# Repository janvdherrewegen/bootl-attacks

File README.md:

# Fill your Boots: Enhanced Embedded Bootloader Exploits via Fault Injection and Binary Analysis

This repository contains source code and data to reproduce results from our paper "Fill your Boots: Enhanced Embedded Bootloader Exploits via Fault Injection and Binary Analysis" at [CHES2021](https://ches.iacr.org/2021/)

## Abstract
The bootloader of an embedded microcontroller is responsible for guarding the device’s internal (flash) memory, enforcing read/write protection mechanisms. Fault injection techniques such as voltage or clock glitching have been proven successful in bypassing such protection for specific microcontrollers, but this often requires expensive equipment and/or exhaustive search of the fault parameters. When multiple glitches are required (e.g., when countermeasures are in place) this search becomes of exponential complexity and thus infeasible. Another challenge which makes embedded bootloaders notoriously hard to analyse is their lack of debugging capabilities.This paper proposes a grey-box approach that leverages binary analysis and advanced software exploitation techniques combined with voltage glitching to develop a powerful attack methodology against embedded bootloaders. We showcase our techniques with three real-world microcontrollers as case studies: 1) we combine static and on-chip dynamic analysis to enable a Return-Oriented Programming exploit on the bootloader of the NXP LPC microcontrollers; 2) we leverage on-chip dynamic analysis on the bootloader of the popular STM8 microcontrollers to constrain the glitch parameter search, achieving the first fully-documented multi-glitch attack on a real-world target; 3) we apply symbolic execution to precisely aim voltage glitches at target instructions based on the execution path in the bootloader of the Renesas 78K0 automotive microcontroller. For each case study, we show that using inexpensive, open-design equipment, we are able to efficiently breach the security of these microcontrollers and get full control of the protected memory, even when multiple glitches are required. Finally, we identify and elaborate on several vulnerable design patterns that should be avoided when implementing embedded bootloaders.

## Dependencies
We use several open source tools and packages to compile and run code on the targets. 

- [k0dasm](https://github.com/mnaberez/k0dasm): A disassembler for the 78k0 
- [as78k0](http://shop-pdp.net/ashtml/as78k0.htm): A compiler for the 78k0
- [aslink](http://shop-pdp.net/ashtml/aslink.htm): A linker for the 78k0
- [sdcc](http://sdcc.sourceforge.net/): Compiler for the stm8
- [naken\_asm](https://github.com/mikeakohn/naken_asm): A disassembler for the stm8
- [stm8flash](https://github.com/vdudouyt/stm8flash):  To flash the stm8 firmware

## Running the code
For the voltage glitching, we use a Raspberry pi3B+ to interface with the GIAnT and the chip under test (cf [Glitch setup](glitch_setup.pdf)). The schematics and source for the GIAnT board is located in the [giant-hardware](giant-hardware) folder.

## Directory Organisation
```
├── 78k0: Code for the 78k0 bootloader analysis (including the symbolic execution framework and glitching code)
├── giant-hardware: Hardware schematics for the new GIAnT board
├── giant-python: Python interface for the GIAnT board
├── lpc: Directory containing the LPC exploit
├── stm8: Code for glitching the STM8
├── README.md
```

## Paper artifacts
The table below clarifies how to recreate the results mentioned in the paper.

| Section | Directory | Commands | Comment |
| ------- | --------- | -------- | ------- |
| 3.2 | ```lpc/ROP``` | ```python3 rop.py```| CRP1 bypass with stack overwrite |
| 3.3 | ```lpc/partial_overwrite``` | ```python3 partial_overwrite.py```| CRP1 bypass with partial flash overwrite |
| 4.1 | ```stm8``` | ```make -C bootloader/```<br>```./flash.sh bootloader/bl_dump.hex option_bytes/STM8AF/opt-rop0-bl0.bin stm8a```| This will flash a firmware to the stm8 which dumps the memory space containing the bootloader over UART |
| 4.2 | ```stm8``` | ```make -C profiling/```<br>```./flash.sh profiling/enter_app.hex option_bytes/STM8AF/opt-rop0-bl0.bin stm8a```<br>```python stm8af_glitch profile``` | This flashes the profiling code and introduces glitches triggered on a GPIO pin |
| 4.3 | ```stm8``` | ```python stm8l_glitch partial_attack``` | Run the glitching on the partially protected stm8l MCU. |
| 4.4 | ```stm8``` | ```python stm8af_glitch full_attack```<br>```python stm8l_glitch full_attack```| Runs the double glitch attack on the STM8 MCUs  |
| 5.1 | ```78k0``` | ```make -C bootloader_dump/```<br>```python glitching/renesas_fpi.py program bootloader/dump_bootl.bin``` | Compiles the code for dumping the 78k0 bootloader. Once flashed, it transmits the code over UART |
| 5.3 | ```78k0/path_constraint``` | ```python2 main.py --db testcases/78k0/checksum_handler.p``` | This command generates the equivalence classes for the checksum handler based on the path through the firmware |
| 5.3 | ```78k0/glitching``` | ```python renesas-78k0-glitch.py``` | This script glitches the checksum command for all equivalence classes output by the path_constraint module |

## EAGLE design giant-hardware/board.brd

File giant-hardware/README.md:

# GIAnT Hardware

This directory contains the schematics for the revised GIAnT board. In line with the previous version, it still uses the (now deprecated) [ZTEX USB-FPGA Module 1.11](https://www.ztex.de/usb-fpga-1/usb-fpga-1.11.e.html). New adopters can order the following components for an alternative:

- [USB-FPGA Module 2.04](https://www.ztex.de/usb-fpga-2/usb-fpga-2.04.e.html): 99 EUR
- [Series 1 Adapter](https://www.ztex.de/usb-fpga-2/1-adapter.e.html): 8 EUR

Including the PCB and all other components, the hardware can be assembled for ~200 USD. [BOM.txt](BOM.txt) contains a detailed Bill of Materials.

## Specifications
With the original composition, the GIAnT offers the following capabilities:

- 10ns minimum pulse width
- 10ns minimum pulse offset
- 145mA max current draw (limited by the [THS3062](https://www.ti.com/store/ti/en/p/product/?p=THS3062D) opamp)

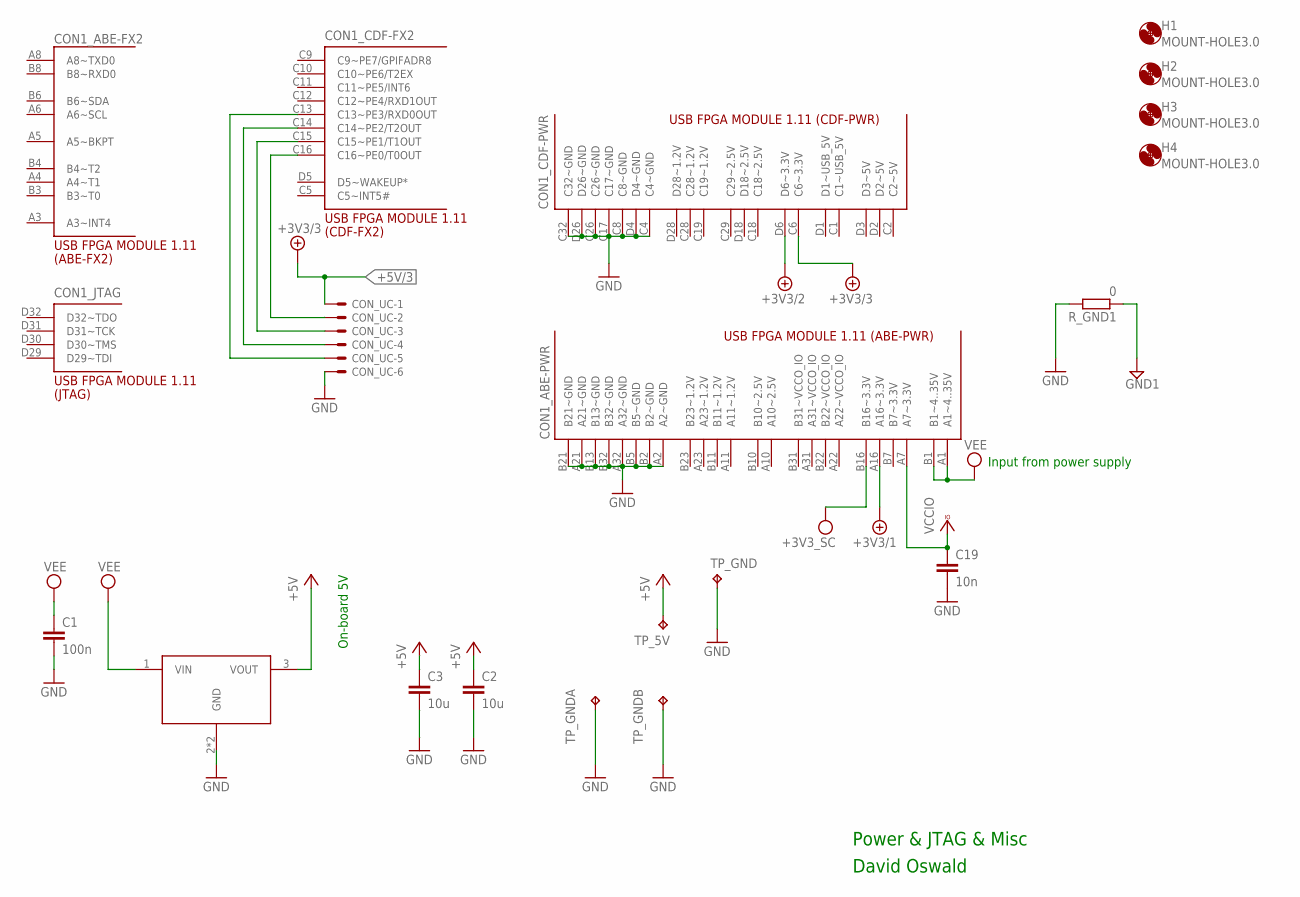
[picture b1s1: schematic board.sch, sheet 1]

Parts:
C1: 100n; C0805K
C2, C3: 10u; C0805K
C19: 10n; C0805K
CON1: USB-FPGA1.11
CON_UC: 22-23-2061
H1, H2, H3, H4: MOUNT-HOLE3.0; 3,0
R_GND1: 0; R0805
TP_5V: TPB1,27; B1,27
TP_GND: TPB1,27; B1,27
TP_GNDA: TPPAD1-13; P1-13
TP_GNDB: TPPAD1-13; P1-13
U$1: MIC5209; SOT223-3

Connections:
+5V: C2.1, C3.1, TP_5V.TP, U$1.3 (VOUT); also elsewhere on the board
+5V/1: CON1.A16 (A16~3.3V); also elsewhere on the board
+5V/2: CON1.D6 (D6~3.3V); also elsewhere on the board
+5V/3: CON1.C6 (C6~3.3V), CON_UC.1; also elsewhere on the board
GND: C1.2, C2.2, C3.2, C19.2, CON1.A2 (A2~GND), CON1.A21 (A21~GND), CON1.A32 (A32~GND), CON1.B2 (B2~GND), CON1.B5 (B5~GND), CON1.B13 (B13~GND), CON1.B21 (B21~GND), CON1.B32 (B32~GND), CON1.C4 (C4~GND), CON1.C8 (C8~GND), CON1.C17 (C17~GND), CON1.C26 (C26~GND), CON1.C32 (C32~GND), CON1.D4 (D4~GND), CON1.D26 (D26~GND), CON_UC.6, R_GND1.2, TP_GND.TP, TP_GNDA.TP, TP_GNDB.TP, U$1.2 (GND), U$1.4 (GND); also elsewhere on the board
GND1: R_GND1.1; also elsewhere on the board
unnamed: CON1.C13 (C13~PE3/RXD0OUT), CON_UC.5
unnamed: CON1.C14 (C14~PE2/T2OUT), CON_UC.4
unnamed: CON1.C15 (C15~PE1/T1OUT), CON_UC.3
unnamed: CON1.C16 (C16~PE0/T0OUT), CON_UC.2
VCCIO: C19.1, CON1.A7 (A7~3.3V); also elsewhere on the board
VEE: C1.1, CON1.A1 (A1~4..35V), CON1.B1 (B1~4..35V), U$1.1 (VIN)
VPP: CON1.B16 (B16~3.3V); also elsewhere on the board

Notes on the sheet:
David Oswald
Power & JTAG & Misc
On-board 5V
Input from power supply

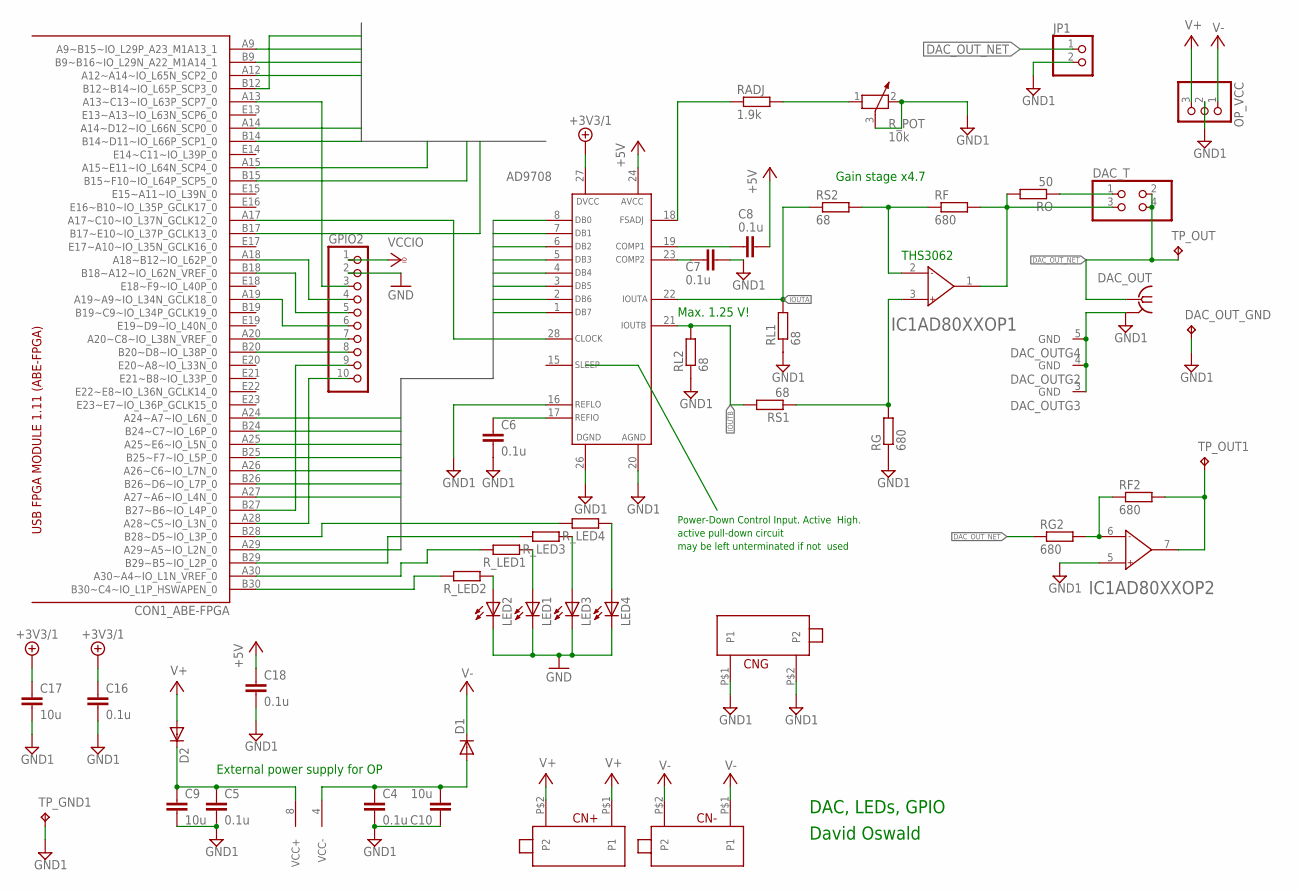
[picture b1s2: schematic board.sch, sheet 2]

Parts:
AD9708: AD7908; SO28W
C4, C5, C6, C7, C8, C16, C18: 0.1u; C0805K
C9, C10, C17: 10u; C0805K
CN+: 24243; 24_243
CN-: 24243; 24_243
CNG: 24243; 24_243
CON1: USB-FPGA1.11
D1, D2: DIODE-SOD123; SOD123
DAC_OUT: BU-SMA-V
DAC_OUT_GND: TPB1,27; B1,27
DAC_T: PINHD-2X2; 2X02
GPIO2: PINHD-1X10; 1X10
IC1: AD80XX; SO08
JP1: PINHD-1X2; 1X02
LED1, LED2, LED3, LED4: LEDCHIPLED_0805; CHIPLED_0805
OP_VCC: PINHD-1X3; 1X03
RADJ: 1.9k; R0805
RF, RF2: 680; R0805
RG, RG2: 680; R0805
RL1, RL2: 68; R0805
RO: 50; R0805
RS1, RS2: 68; R0805
R_LED1, R_LED2, R_LED3, R_LED4: R-EU_R0805; R0805
R_POT: 10k; PT-SPIN
TP_GND1: TPB1,27; B1,27
TP_OUT, TP_OUT1: TPB1,27; B1,27

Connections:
+5V: AD9708.24 (AVCC), C8.1, C18.1; also elsewhere on the board
+5V/1: AD9708.27 (DVCC), C16.1, C17.1; also elsewhere on the board
CLK: AD9708.28 (CLOCK), CON1.A17 (A17~C10~IO_L37N_GCLK12_0)
CLK_SC: CON1.A15 (A15~E11~IO_L64N_SCP4_0); also elsewhere on the board
COMP1: AD9708.19 (COMP1), C8.2
COMP2: AD9708.23 (COMP2), C7.1
DAC_OUT_NET: DAC_OUT.1, DAC_T.2, DAC_T.4, JP1.1, RG2.1, TP_OUT.TP
DB0: AD9708.8 (DB0), CON1.A29 (A29~A5~IO_L2N_0)
DB1: AD9708.7 (DB1), CON1.A27 (A27~A6~IO_L4N_0)
DB2: AD9708.6 (DB2), CON1.B26 (B26~D6~IO_L7P_0)
DB3: AD9708.5 (DB3), CON1.A26 (A26~C6~IO_L7N_0)
DB4: AD9708.4 (DB4), CON1.A25 (A25~E6~IO_L5N_0)
DB5: AD9708.3 (DB5), CON1.B25 (B25~F7~IO_L5P_0)
DB6: AD9708.2 (DB6), CON1.A24 (A24~A7~IO_L6N_0)
DB7: AD9708.1 (DB7), CON1.B24 (B24~C7~IO_L6P_0)
FSADJ: AD9708.18 (FSADJ), RADJ.1
GND: GPIO2.2, LED1.C, LED2.C, LED3.C, LED4.C; also elsewhere on the board
GND1: AD9708.16 (REFLO), AD9708.20 (AGND), AD9708.26 (DGND), C4.2, C5.2, C6.2, C7.2, C9.2, C10.1, C16.2, C17.2, C18.2, CNG.P$1 (P1), CNG.P$2 (P2), DAC_OUT.2 (GND), DAC_OUT.3 (GND), DAC_OUT.4 (GND), DAC_OUT.5 (GND), DAC_OUT_GND.TP, IC1.5 (IN+), JP1.2, OP_VCC.2, RG.1, RL1.1, RL2.1, R_POT.2, R_POT.3, TP_GND1.TP; also elsewhere on the board
IO: CON1.B9 (B9~B16~IO_L29N_A22_M1A14_1); also elsewhere on the board
IOUTA: AD9708.22 (IOUTA), RL1.2, RS2.1
IOUTB: AD9708.21 (IOUTB), RL2.2, RS1.2
unnamed: CON1.A13 (A13~C13~IO_L63P_SCP7_0), GPIO2.3
unnamed: CON1.A18 (A18~B12~IO_L62P_0), GPIO2.4
unnamed: CON1.B18 (B18~A12~IO_L62N_VREF_0), GPIO2.5
unnamed: CON1.A19 (A19~A9~IO_L34N_GCLK18_0), GPIO2.6
unnamed: CON1.A20 (A20~C8~IO_L38N_VREF_0), GPIO2.7
unnamed: CON1.B20 (B20~D8~IO_L38P_0), GPIO2.8
unnamed: CON1.B27 (B27~B6~IO_L4P_0), GPIO2.9
unnamed: CON1.A28 (A28~C5~IO_L3N_0), GPIO2.10
unnamed: IC1.3 (IN+), RG.2, RS1.1
unnamed: IC1.2 (IN-), RF.1, RS2.2
unnamed: DAC_T.3, IC1.1 (OUT), RF.2, RO.2
unnamed: DAC_T.1, RO.1
unnamed: RADJ.2, R_POT.1
unnamed: IC1.6 (IN-), RF2.1, RG2.2
unnamed: IC1.7 (OUT), RF2.2, TP_OUT1.TP
unnamed: LED2.A, R_LED2.1
unnamed: LED1.A, R_LED1.1
unnamed: LED3.A, R_LED3.1
unnamed: LED4.A, R_LED4.1
unnamed: CON1.B30 (B30~C4~IO_L1P_HSWAPEN_0), R_LED2.2
unnamed: CON1.A30 (A30~A4~IO_L1N_VREF_0), R_LED1.2
unnamed: CON1.B29 (B29~B5~IO_L2P_0), R_LED3.2
unnamed: CON1.B28 (B28~D5~IO_L3P_0), R_LED4.2
PIN4: CON1.B14 (B14~D11~IO_L66P_SCP1_0); also elsewhere on the board
PIN6: CON1.A12 (A12~A14~IO_L65N_SCP2_0); also elsewhere on the board
PIN8: CON1.A9 (A9~B15~IO_L29P_A23_M1A13_1); also elsewhere on the board
REFIO: AD9708.17 (REFIO), C6.1
RST: CON1.B15 (B15~F10~IO_L64P_SCP5_0); also elsewhere on the board
SHDN: CON1.B17 (B17~E10~IO_L37P_GCLK13_0); also elsewhere on the board
SW1: CON1.B12 (B12~B14~IO_L65P_SCP3_0)
SW2: CON1.A14 (A14~D12~IO_L66N_SCP0_0)
V+: CN+.P$1 (P1), CN+.P$2 (P2), D2.A, OP_VCC.3
V-: CN-.P$1 (P1), CN-.P$2 (P2), D1.C, OP_VCC.1
VCC+: C5.1, C9.1, D2.C, IC1.8 (VCC+)
VCC-: C4.1, C10.2, D1.A, IC1.4 (VCC-)
VCCIO: GPIO2.1; also elsewhere on the board

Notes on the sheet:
David Oswald
DAC, LEDs, GPIO
Max. 1.25 V!
Gain stage x4.7
Power-Down Control Input. Active High.
active pull-down circuit
may be left unterminated if not used
THS3062
External power supply for OP

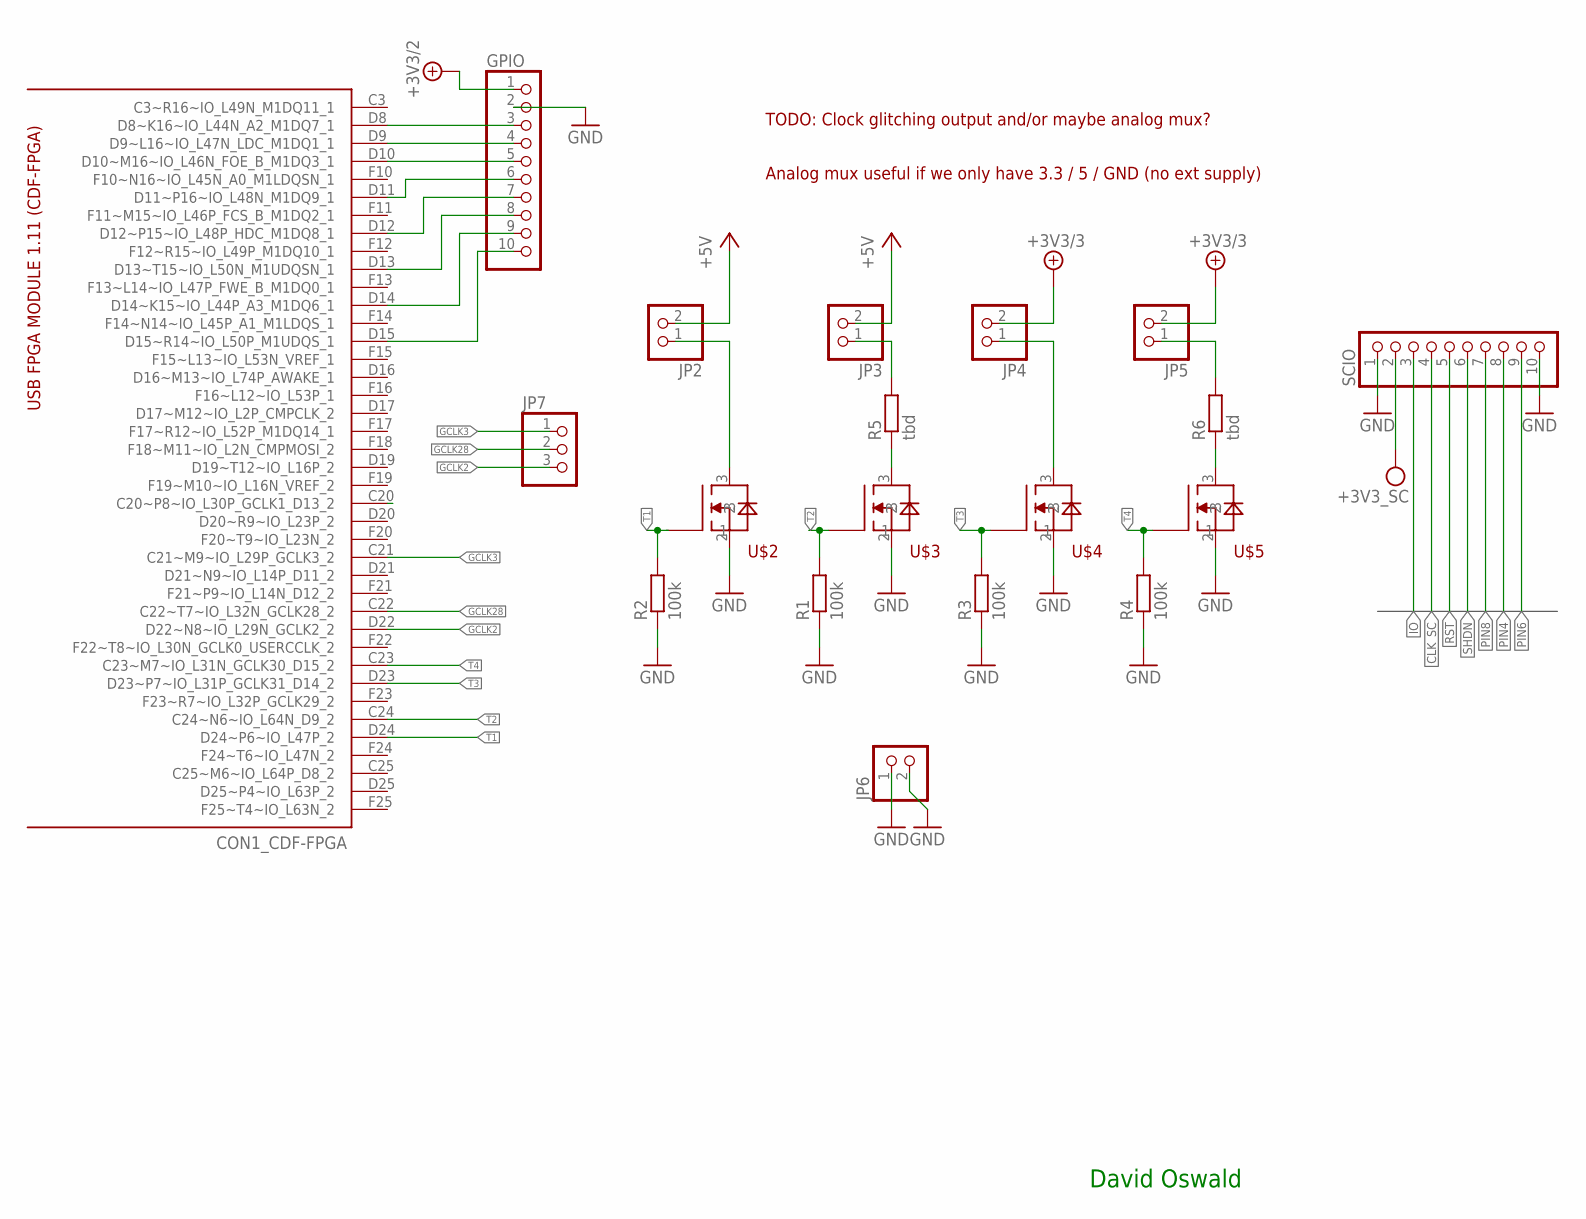
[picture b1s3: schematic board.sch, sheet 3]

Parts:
CON1: USB-FPGA1.11
GPIO: PINHD-1X10; 1X10
JP2, JP3, JP4, JP5, JP6: PINHD-1X2; 1X02
JP7: PINHD-1X3; 1X03
R1, R2, R3, R4: 100k; M0805
R5, R6: tbd; M0805
SCIO: PINHD-1X10; 1X10
U$2, U$3, U$4, U$5: DMG1012UW; DMG1012UW1-SMT323

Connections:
+5V: JP2.2, JP3.2; also elsewhere on the board
+5V/2: GPIO.1; also elsewhere on the board
+5V/3: JP4.2, JP5.2; also elsewhere on the board
CLK_SC: SCIO.4; also elsewhere on the board
GCLK2: CON1.D22 (D22~N8~IO_L29N_GCLK2_2), JP7.3
GCLK3: CON1.C21 (C21~M9~IO_L29P_GCLK3_2), JP7.1
GCLK28: CON1.C22 (C22~T7~IO_L32N_GCLK28_2), JP7.2
GND: GPIO.2, JP6.1, JP6.2, R1.1, R2.1, R3.1, R4.1, SCIO.1, SCIO.10, U$2.2, U$3.2, U$4.2, U$5.2; also elsewhere on the board
IO: SCIO.3; also elsewhere on the board
unnamed: R5.1, U$3.3
unnamed: JP2.1, U$2.3
unnamed: JP3.1, R5.2
unnamed: R6.1, U$5.3
unnamed: JP4.1, U$4.3
unnamed: JP5.1, R6.2
unnamed: CON1.D8 (D8~K16~IO_L44N_A2_M1DQ7_1), GPIO.3
unnamed: CON1.D9 (D9~L16~IO_L47N_LDC_M1DQ1_1), GPIO.4
unnamed: CON1.D10 (D10~M16~IO_L46N_FOE_B_M1DQ3_1), GPIO.5
unnamed: CON1.D11 (D11~P16~IO_L48N_M1DQ9_1), GPIO.6
unnamed: CON1.D12 (D12~P15~IO_L48P_HDC_M1DQ8_1), GPIO.7
unnamed: CON1.D13 (D13~T15~IO_L50N_M1UDQSN_1), GPIO.8
unnamed: CON1.D14 (D14~K15~IO_L44P_A3_M1DQ6_1), GPIO.9
unnamed: CON1.D15 (D15~R14~IO_L50P_M1UDQS_1), GPIO.10
PIN4: SCIO.8; also elsewhere on the board
PIN6: SCIO.9; also elsewhere on the board
PIN8: SCIO.7; also elsewhere on the board
RST: SCIO.5; also elsewhere on the board
SHDN: SCIO.6; also elsewhere on the board
T1: CON1.D24 (D24~P6~IO_L47P_2), R2.2, U$2.1
T2: CON1.C24 (C24~N6~IO_L64N_D9_2), R1.2, U$3.1
T3: CON1.D23 (D23~P7~IO_L31P_GCLK31_D14_2), R3.2, U$4.1
T4: CON1.C23 (C23~M7~IO_L31N_GCLK30_D15_2), R4.2, U$5.1
VPP: SCIO.2; also elsewhere on the board

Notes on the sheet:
David Oswald
TODO: Clock glitching output and/or maybe analog mux?
Analog mux useful if we only have 3.3 / 5 / GND (no ext supply)

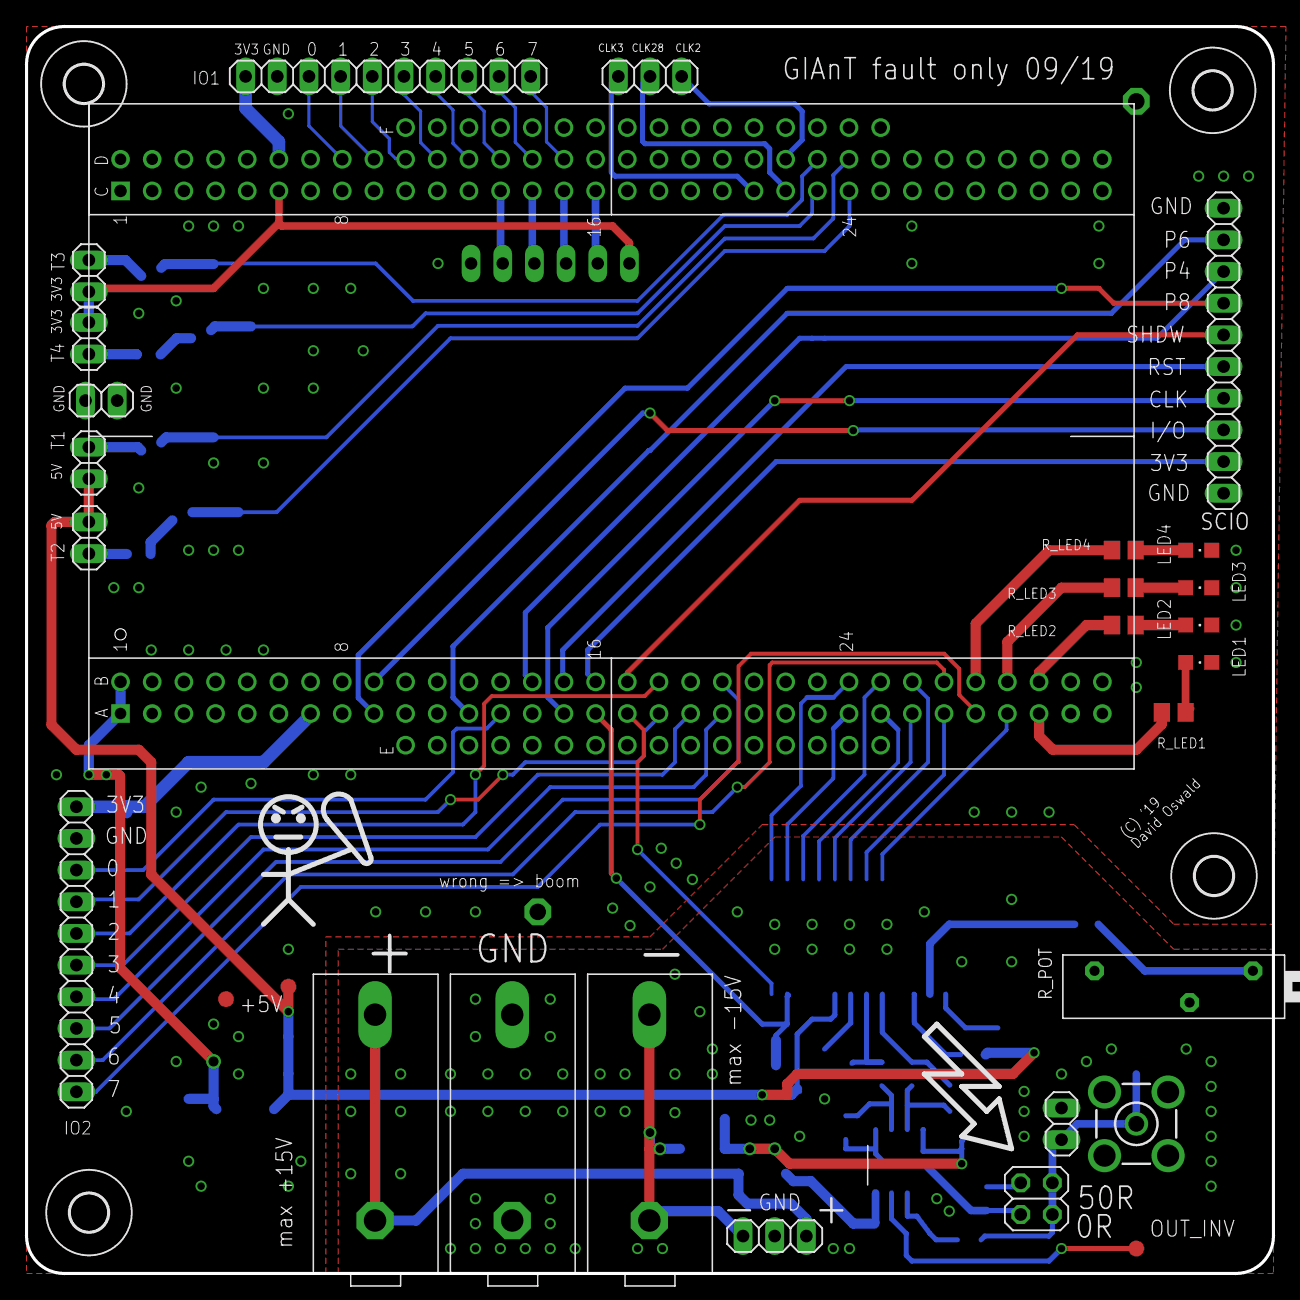
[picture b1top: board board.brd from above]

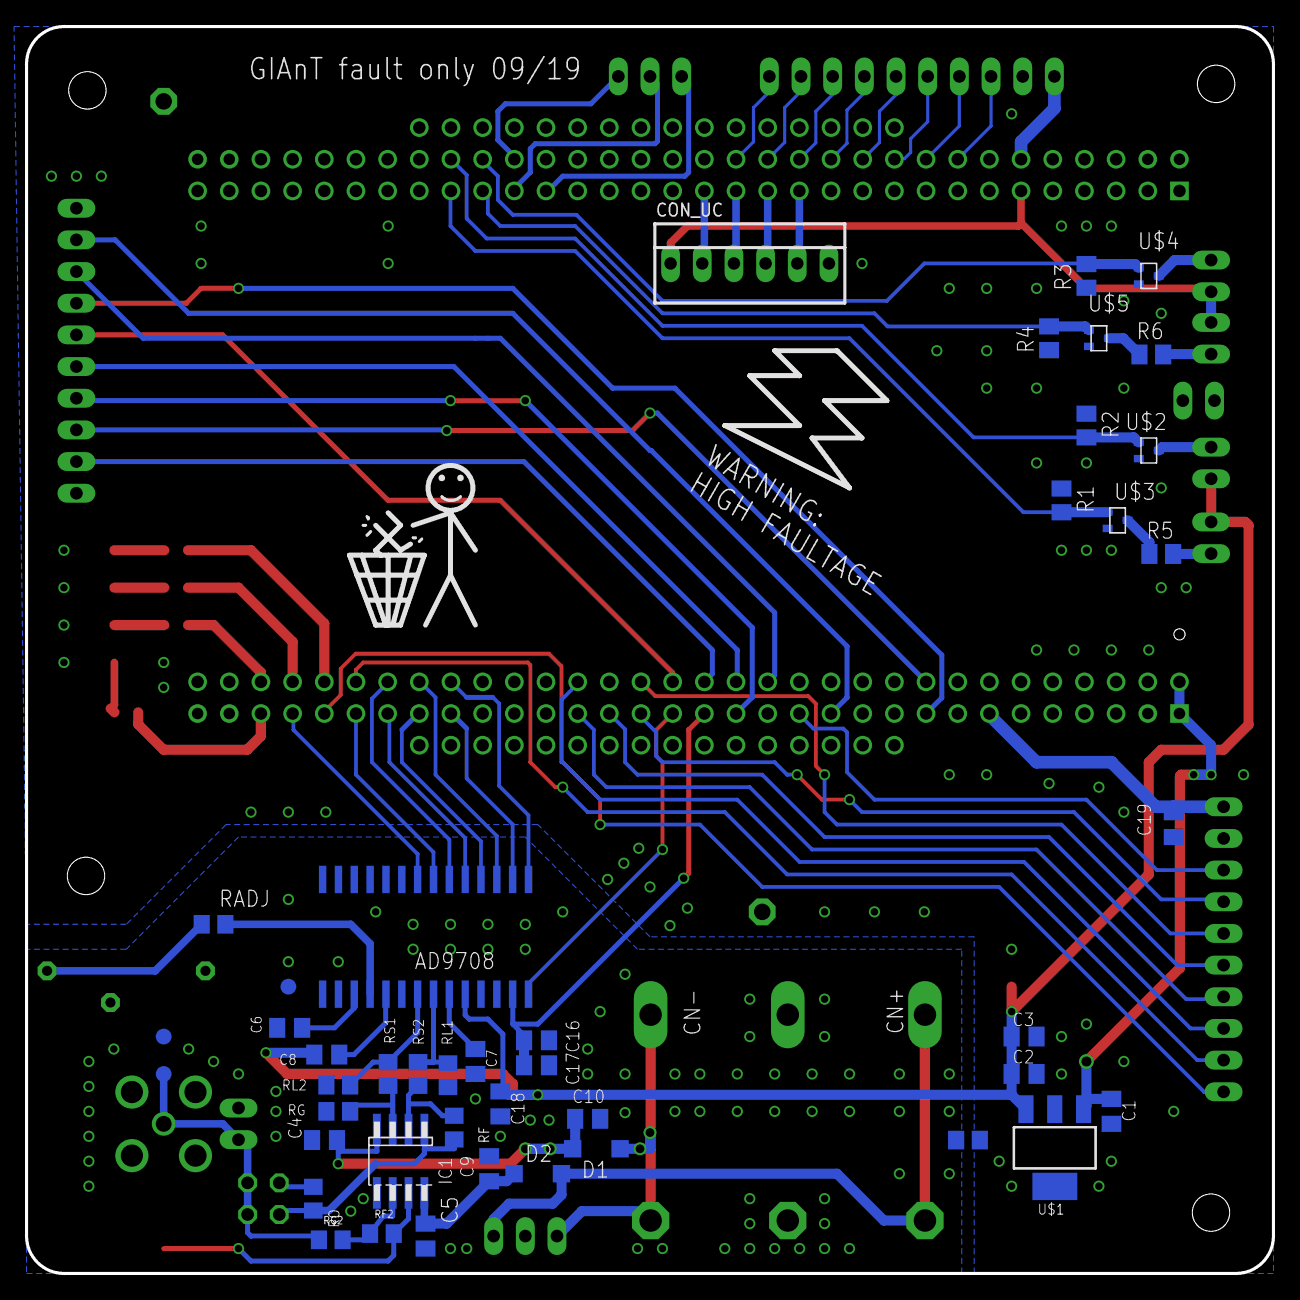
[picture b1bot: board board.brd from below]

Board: 2 copper layers, 100.0 x 100.0 mm, 79 parts (44 on the bottom side), 84 nets.

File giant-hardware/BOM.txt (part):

Partlist exported from /home/jeanjean/PhD/Jan/bootl-attacks/paper_repo/giant-hardware/board.sch at 13/01/2021 17:12

Part        Value         Device                Package           Description                            MF MPN OC_FARNELL OC_NEWARK TP_SIGNAL_NAME
AD9708      AD7908        AD7908                SO28W             AD9708 8-Bit DAC with current output                                             
C1          100n          C-EUC0805K            C0805K            CAPACITOR, European symbol                                                       
C2          10u           C-EUC0805K            C0805K            CAPACITOR, European symbol                                                       
C3          10u           C-EUC0805K            C0805K            CAPACITOR, European symbol                                                       
C4          0.1u          C-EUC0805K            C0805K            CAPACITOR, European symbol                                                       
C5          0.1u          C-EUC0805K            C0805K            CAPACITOR, European symbol                                                       
C6          0.1u          C-EUC0805K            C0805K            CAPACITOR, European symbol                                                       
C7          0.1u          C-EUC0805K            C0805K            CAPACITOR, European symbol                                                       
C8          0.1u          C-EUC0805K            C0805K            CAPACITOR, European symbol                                                       
C9          10u           C-EUC0805K            C0805K            CAPACITOR, European symbol                                                       
C10         10u           C-EUC0805K            C0805K            CAPACITOR, European symbol                                                       
C16         0.1u          C-EUC0805K            C0805K            CAPACITOR, European symbol                                                       
C17         10u           C-EUC0805K            C0805K            CAPACITOR, European symbol                                                       
C18         0.1u          C-EUC0805K            C0805K            CAPACITOR, European symbol                                                       
C19         10n           C-EUC0805K            C0805K            CAPACITOR, European symbol                                                       
CN+         24243         24243                 24_243            Multicomp 24.243 Series                                                          
CN-         24243         24243                 24_243            Multicomp 24.243 Series                                                          
CNG         24243         24243                 24_243            Multicomp 24.243 Series                                                          
CON1        USB-FPGA1.11  USB-FPGA1.11          USB-FPGA1.11                                                                                       
CON_UC                    22-23-2061            22-23-2061        .100" (2.54mm) Center Header - 6 Pin                                             
D1                        DIODE-SOD123          SOD123            DIODE                                                                            
D2                        DIODE-SOD123          SOD123            DIODE                                                                            
DAC_OUT                   BU-SMA-V              BU-SMA-V          FEMALE SMA CONNECTOR                          unknown    unknown                 
DAC_OUT_GND TPB1,27       TPB1,27               B1,27             Test pad                                                                         
DAC_T                     PINHD-2X2             2X02              PIN HEADER                                                                       
GPIO                      PINHD-1X10            1X10              PIN HEADER                                                                       
GPIO2                     PINHD-1X10            1X10              PIN HEADER                                                                       
H1          MOUNT-HOLE3.0 MOUNT-HOLE3.0         3,0               MOUNTING HOLE with drill center marker                                           
H2          MOUNT-HOLE3.0 MOUNT-HOLE3.0         3,0               MOUNTING HOLE with drill center marker                                           
H3          MOUNT-HOLE3.0 MOUNT-HOLE3.0         3,0               MOUNTING HOLE with drill center marker                                           
H4          MOUNT-HOLE3.0 MOUNT-HOLE3.0         3,0               MOUNTING HOLE with drill center marker                                           
IC1         AD80XX        AD80XX                SO08              AD high bandwidth dual opamp                                                     
JP1                       PINHD-1X2             1X02              PIN HEADER                                                                       
JP2                       PINHD-1X2             1X02              PIN HEADER                                                                       
JP3                       PINHD-1X2             1X02              PIN HEADER                                                                       
JP4                       PINHD-1X2             1X02              PIN HEADER                                                                       
JP5                       PINHD-1X2             1X02              PIN HEADER                                                                       
JP6                       PINHD-1X2             1X02              PIN HEADER                                                                       
JP7                       PINHD-1X3             1X03              PIN HEADER                                                                       
LED1                      LEDCHIPLED_0805       CHIPLED_0805      LED                                                                              
LED2                      LEDCHIPLED_0805       CHIPLED_0805      LED                                                                              
LED3                      LEDCHIPLED_0805       CHIPLED_0805      LED                                                                              
LED4                      LEDCHIPLED_0805       CHIPLED_0805      LED                                                                              
OP_VCC                    PINHD-1X3             1X03              PIN HEADER                                                                       
R1          100k          R-EU_M0805            M0805             RESISTOR, European symbol                                                        
R2          100k          R-EU_M0805            M0805             RESISTOR, European symbol                                                        
R3          100k          R-EU_M0805            M0805             RESISTOR, European symbol                                                        
R4          100k          R-EU_M0805            M0805             RESISTOR, European symbol                                                        
R5          tbd           R-EU_M0805            M0805             RESISTOR, European symbol                                                        
R6          tbd           R-EU_M0805            M0805             RESISTOR, European symbol                                                        
RADJ        1.9k          R-EU_R0805            R0805             RESISTOR, European symbol                                                        
RF          680           R-EU_R0805            R0805             RESISTOR, European symbol                                                        
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
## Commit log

2020-10-21 Add giant-python folder and stm8 dir
2020-10-21 Added readme
2020-10-23 STM8 doc + option bytes + README
2020-10-24 Added lpc folder based on Qais' github
2020-10-28 Added Giant board/schematic and PDFs
2020-11-02 Added code to dump bootloader and bootloader binary
2020-11-02 Added documentation
2020-11-02 Added path constraint directory
2020-11-02 Added license and updated README
2020-11-02 Added submodules
2020-11-02 Added glitch setup
2020-11-03 Added flash script to stm8 dir
2020-11-03 Added stm8 example flash files and modified README
2020-11-03 Added 78k0 glitch directory
2020-11-03 Modified README files
2020-11-04 Improved LPC exploit documentation
2020-11-04 Added dumper code and binary
2020-11-04 Edited README
2020-11-16 More info on 78k0 attack - added stm8 part numbers
2020-11-16 Added GIAnT hardware alternative
2020-11-18 Added ZTEX series 2 fpga files
2020-12-01 Added command line parsing to 78k0 scripts and added assembler and linker
2020-12-01 Added profiling code for stm8. Added command line parsing of arguments for the glitch scripts
2020-12-01 Added step by step guide for artifact reproduction
2020-12-07 Added scripts for lpc exploits
2020-12-08 Removed submodules
2020-12-08 Fixed argparse
2020-12-08 Fixed argparse issues
2021-01-13 Added bill of materials & requirements for GIAnT
2021-01-13 Fixed extra ack in stm8 get_bootl
